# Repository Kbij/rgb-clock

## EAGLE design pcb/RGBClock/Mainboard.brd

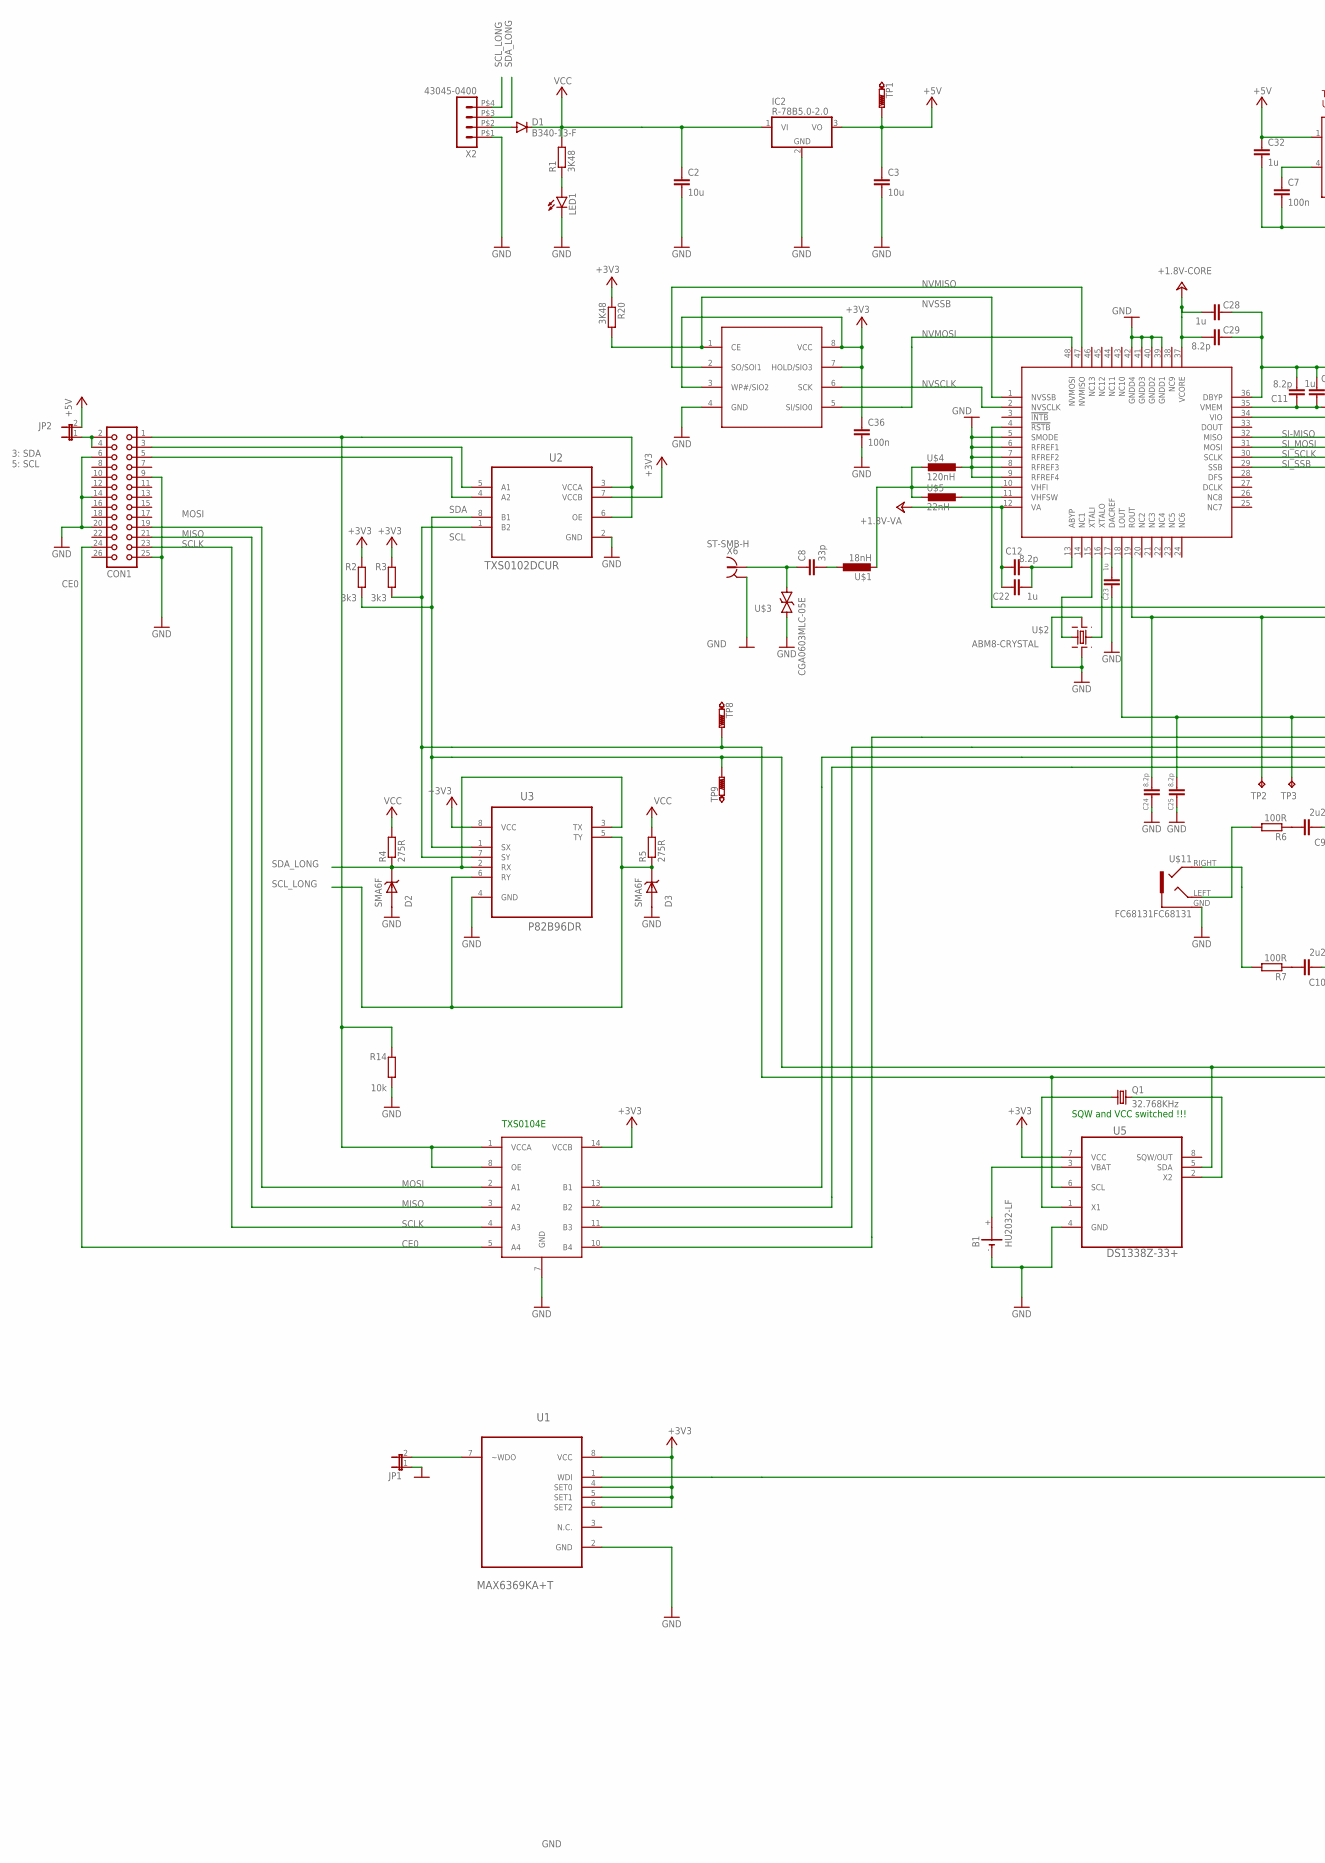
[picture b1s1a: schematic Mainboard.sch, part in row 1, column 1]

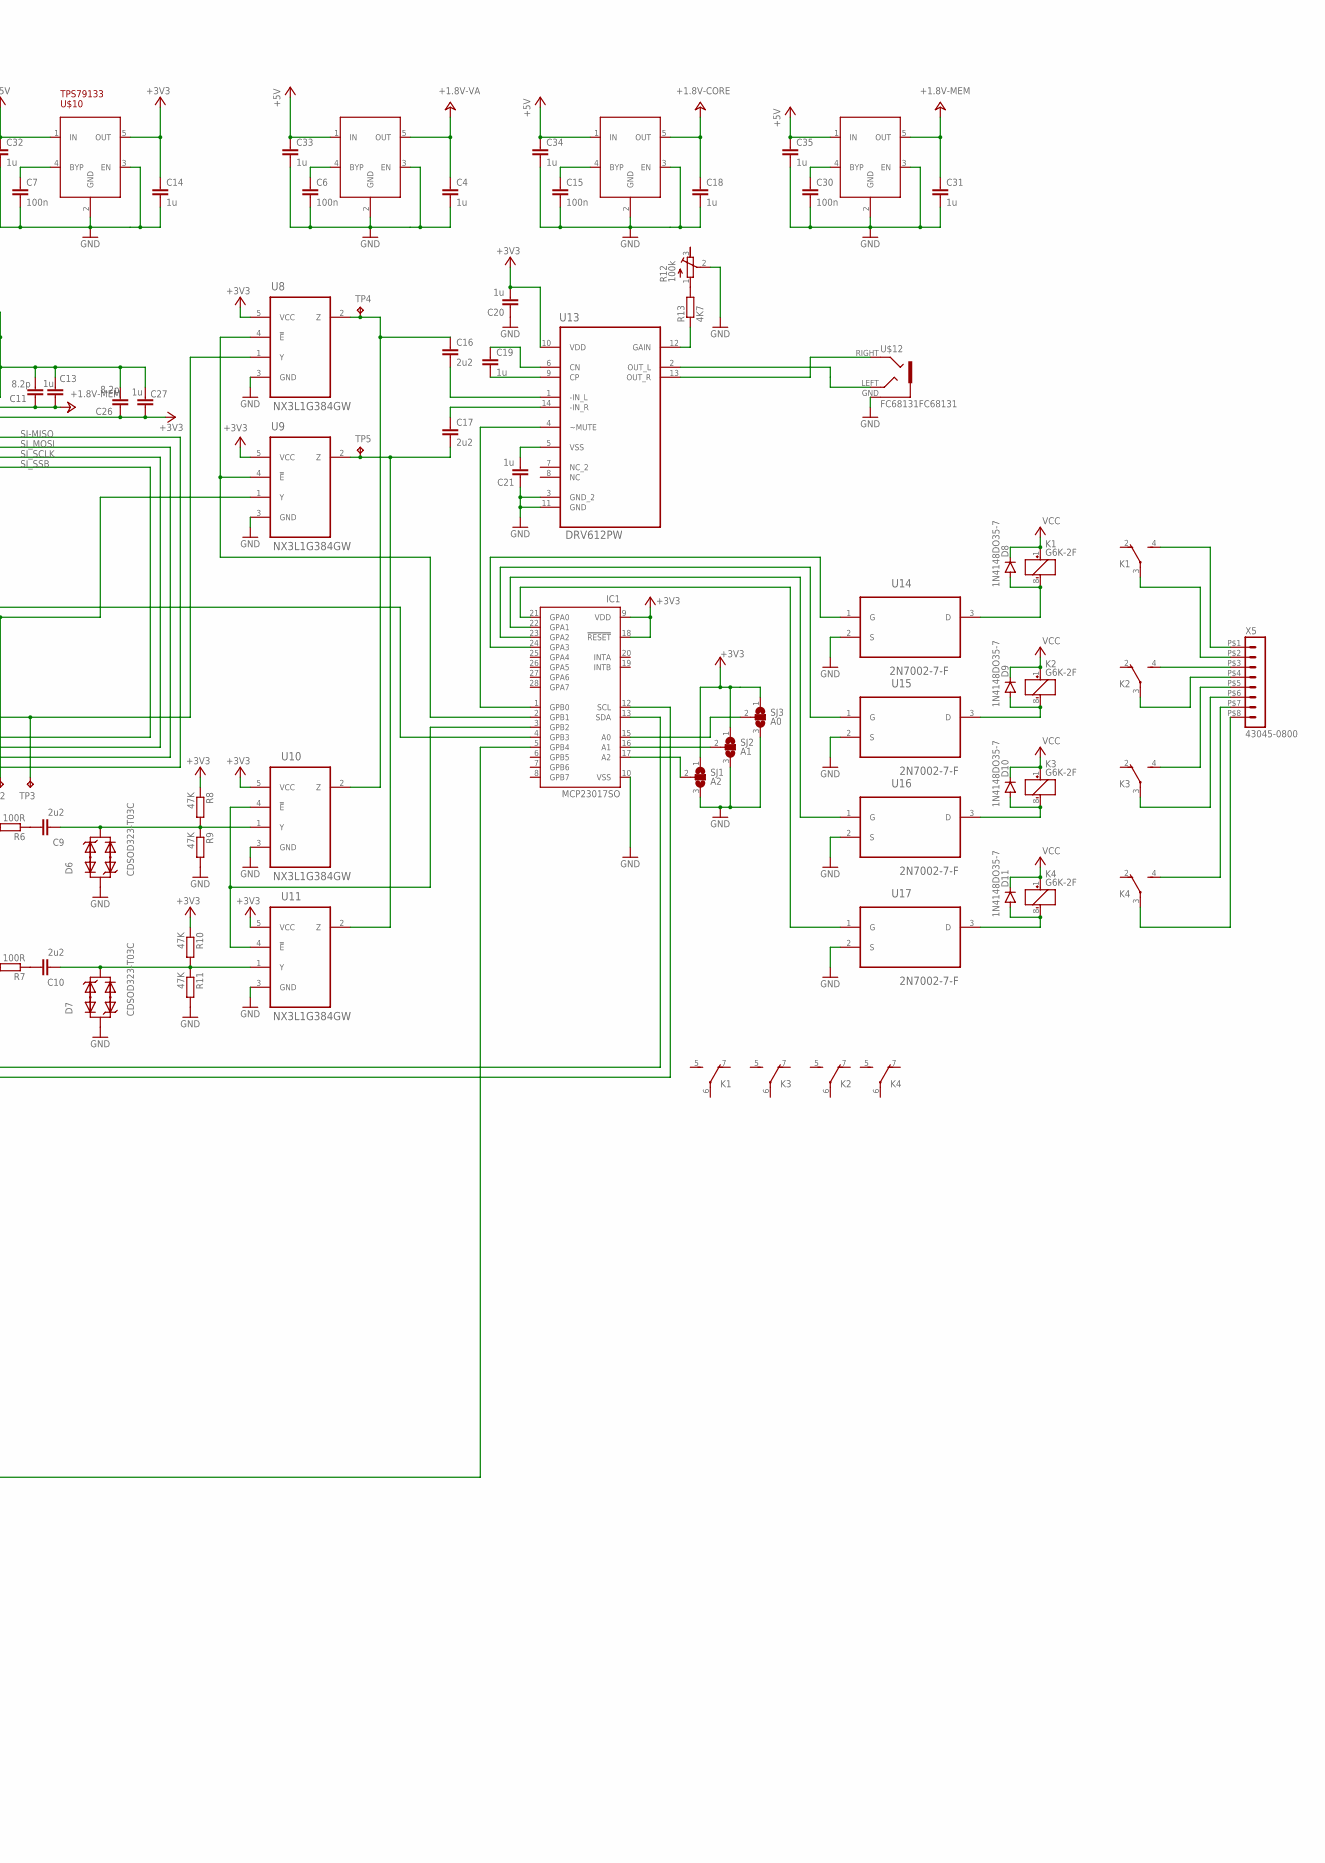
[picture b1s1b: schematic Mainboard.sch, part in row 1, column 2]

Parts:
B1: HU2032-LF; MYCOMPONENTS_HU2032-LF
C2, C3: 10u; RCL_C1206
C4, C13, C14, C18, C22, C23, C27, C28, C31, C32, C33, C34, C35: 1u; RCL_C0805
C6, C7, C15, C30, C36: 100n; RCL_C0805
C8: 33p; RCL_C0805
C9, C10, C16, C17: 2u2; RCL_C0805
C11, C12, C24, C25, C26, C29: 8.2p; RCL_C0805
C19, C20, C21: 1u; RCL_C1005
CON1: CON26
D1: B340-13-F; DIODE_DO-214AC
D2, D3: SMA6F; MYCOMPONENTS_DO-221AC
D6, D7: CDSOD323-T03C; MYCOMPONENTS_SOD323
D8, D9, D10, D11: 1N4148DO35-7; DIODE_DO35-7
IC1: MCP23017SO; MICROCHIP_SO28W
IC2: R-78B5.0-2.0; TO220V
JP1, JP2: JUMPER_JP1E; JUMPER_JP1
K1, K2, K3, K4: G6K-2F; RELAY_G6K-2F
LED1: LEDCHIP-LED0805; CHIP-LED0805
Q1: 32.768KHz; CRYSTAL_TC26V
R1, R20: 3K48; M0805
R2, R3: 3k3; M0805
R4, R5: 275R; M0805
R6, R7: 100R; M0805
R8, R9, R10, R11: 47K; M0805
R12: 100k; RESISTOR_RTRIM4G/J
R13: 4K7; M0805
R14: 10k; M0805
SJ1: A2; SJ_2
SJ2: A1; SJ_2
SJ3: A0; SJ_2
SPI: TXS0104E; TEXAS_SOP65P640X120-14N
TP1, TP8, TP9: PTR1PAD1-13; P1-13
TP2, TP3, TP4, TP5: TESTPAD_TPTP07SQ; TESTPAD_TP07SQ
U1: MAX6369KA+T; MAXIM_BY_ELEMENT14_BATCH_1_SOT65P280X145-8N
U2: TXS0102DCUR; TEXAS_SOP50P310X90-8N
U3: P82B96DR; TEXAS_SOIC127P600X175-8N
U5: DS1338Z-33+; MAXIM_BY_ELEMENT14_BATCH_1_SOIC127P600X175-8N
U8, U9, U10, U11: NX3L1G384GW; NXP_BY_ELEMENT14_BATCH_1_SOT65P212X110-5N
U13: DRV612PW; TEXAS_SOP65P640X120-14N
U14, U15, U16, U17: 2N7002-7-F; DIODES_SOT103P240X110-3N
U$1: 18nH; MAINBOARD_0603
U$2: ABM8-CRYSTAL; ABM8
U$3: CGA0603MLC-05E; MAINBOARD_C0603K
U$4: 120nH; MAINBOARD_0603
U$5: 22nH; MAINBOARD_0603
U$6: SI4684-MYSMD; QFN48-SI4684
U$7, U$8, U$9: TPS79118; SOT23-5
U$10: TPS79133; SOT23-5
U$11, U$12: FC68131FC68131; FC68131
U$13: SST26VF032B; SOIJ8
X2: 43045-0400; CON-MOLEX-MICRO-FIT-3_0_43045-0400
X5: 43045-0800; CON-MOLEX-MICRO-FIT-3_0_43045-0800
X6: ST-SMB-H; MAINBOARD_ST-SMB-H

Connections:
+1.8-MEM: C11.1, C13.1, C31.1, U$6.35 (VMEM), U$9.5 (OUT)
+1.8-VA: C4.1, C12.1, C22.1, U$6.12 (VA), U$7.5 (OUT)
+1.8-VCORE: C18.1, C28.2, C29.2, U$6.37 (VCORE), U$8.5 (OUT)
+3V3: C14.1, C20.2, C26.1, C27.1, C36.1, IC1.9 (VDD), IC1.18 (!RESET), R2.2, R3.2, R8.1, R10.1, R20.1, SJ1.1, SJ2.1, SJ3.1, SPI.14 (VCCB), U1.4 (SET0), U1.5 (SET1), U1.6 (SET2), U1.8 (VCC), U2.7 (VCCB), U3.8 (VCC), U5.7 (VCC), U8.5 (VCC), U9.5 (VCC), U10.5 (VCC), U11.5 (VCC), U13.10 (VDD), U$6.34 (VIO), U$10.5 (OUT), U$13.3 (WP#/SIO2), U$13.7 (HOLD/SIO3), U$13.8 (VCC)
+5V: C3.1, C32.1, C33.1, C34.1, C35.1, IC2.3 (VO), JP2.2, TP1.TP, U$7.1 (IN), U$8.1 (IN), U$9.1 (IN), U$10.1 (IN)
CE0: CON1.24, SPI.5 (A4)
GND: B1.-, C2.2, C3.2, C4.2, C6.2, C7.2, C14.2, C15.2, C18.2, C20.1, C21.1, C23.1, C24.1, C25.1, C30.2, C31.2, C32.2, C33.2, C34.2, C35.2, C36.2, CON1.6, CON1.9, CON1.14, CON1.20, CON1.25, D2.AN, D3.AN, D6.P$1, D7.P$1, IC1.10 (VSS), IC2.2 (GND), JP1.1, LED1.C, R9.2, R11.2, R12.2 (S), R14.1, SJ1.3, SJ2.3, SJ3.3, SPI.7 (GND), U1.2 (GND), U2.2 (GND), U3.4 (GND), U5.4 (GND), U8.3 (GND), U9.3 (GND), U10.3 (GND), U11.3 (GND), U13.3 (GND_2), U13.11 (GND), U14.2 (S), U15.2 (S), U16.2 (S), U17.2 (S), U$2.1 (GND1), U$2.3 (GND2), U$3.1, U$4.1, U$6.5 (SMODE), U$6.6 (RFREF1), U$6.7 (RFREF2), U$6.8 (RFREF3), U$6.9 (RFREF4), U$6.39 (GNDD1), U$6.40 (GNDD2), U$6.41 (GNDD3), U$6.42 (GNDD4), U$7.2 (GND), U$7.3 (EN), U$8.2 (GND), U$8.3 (EN), U$9.2 (GND), U$9.3 (EN), U$10.2 (GND), U$10.3 (EN), U$11.GND, U$12.GND, U$13.4 (GND), X2.P$1 (1), X6.2, X6.3 (2), X6.4 (2), X6.5 (2)
MISO: CON1.21, SPI.3 (A2)
MOSI: CON1.19, SPI.2 (A1)
unnamed: D1.A, X2.P$2 (2)
unnamed: U$2.2 (1), U$6.15 (XTALI)
unnamed: CON1.3, U2.5 (A1)
unnamed: CON1.2, CON1.4, JP2.1
unnamed: K1.4 (S), X5.P$1 (1)
unnamed: CON1.5, U2.4 (A2)
unnamed: IC1.21 (GPA0), U17.1 (G)
unnamed: CON1.1, R14.2, SPI.1 (VCCA), SPI.8 (OE), U2.3 (VCCA), U2.6 (OE)
unnamed: D11.A, K4.8 (-), U17.3 (D)
unnamed: IC1.17 (A2), SJ1.2
unnamed: IC1.16 (A1), SJ2.2
unnamed: K4.4 (S), X5.P$7 (7)
unnamed: K4.3, X5.P$8 (8)
unnamed: LED1.A, R1.1
unnamed: Q1.2, U5.2 (X2)
unnamed: B1.+, U5.3 (VBAT)
unnamed: Q1.1, U5.1 (X1)
unnamed: IC1.24 (GPA3), U14.1 (G)
unnamed: IC1.23 (GPA2), U15.1 (G)
unnamed: K1.3, X5.P$2 (2)
unnamed: IC1.22 (GPA1), U16.1 (G)
unnamed: D8.A, K1.8 (-), U14.3 (D)
unnamed: D9.A, K2.8 (-), U15.3 (D)
unnamed: D10.A, K3.8 (-), U16.3 (D)
unnamed: U$2.4 (2), U$6.16 (XTALO)
unnamed: C25.2, TP3.TP, U8.1 (Y), U$6.18 (LOUT)
unnamed: C8.1, U$3.2, X6.1
unnamed: C16.1, TP4.TP, U8.2 (Z), U10.2 (Z)
unnamed: C17.2, TP5.TP, U9.2 (Z), U11.2 (Z)
unnamed: IC1.3 (GPB2), U10.4 (!E), U11.4 (!E)
unnamed: U$5.1, U$6.11 (VHFSW)
unnamed: IC1.5 (GPB4), U1.1 (WDI)
unnamed: C24.2, TP2.TP, U9.1 (Y), U$6.19 (ROUT)
unnamed: IC1.4 (GPB3), U$6.4 (!RSTB)
unnamed: C10.2, D7.P$2, R10.2, R11.1, U11.1 (Y)
unnamed: C9.2, D6.P$2, R8.2, R9.1, U10.1 (Y)
unnamed: IC1.1 (GPB0), U13.4 (~MUTE)
unnamed: C6.1, U$7.4 (BYP)
unnamed: U13.2 (OUT_L), U$12.LEFT
unnamed: IC1.15 (A0), SJ3.2
unnamed: U13.13 (OUT_R), U$12.RIGHT
unnamed: R12.1 (E), R13.2
unnamed: R13.1, U13.12 (GAIN)
unnamed: R6.2, U$11.LEFT
unnamed: C9.1, R6.1
unnamed: R7.2, U$11.RIGHT
unnamed: C10.1, R7.1
unnamed: JP1.2, U1.7 (~WDO)
unnamed: K2.4 (S), X5.P$3 (3)
unnamed: C16.2, U13.1 (-IN_L)
unnamed: C19.2, U13.9 (CP)
unnamed: C17.1, U13.14 (-IN_R)
unnamed: C19.1, U13.6 (CN)
unnamed: C21.2, U13.5 (VSS)
unnamed: C15.1, U$8.4 (BYP)
unnamed: U$1.2, U$4.2, U$5.2, U$6.10 (VHFI)
unnamed: K2.3, X5.P$4 (4)
unnamed: C8.2, U$1.1
unnamed: C30.1, U$9.4 (BYP)
unnamed: K3.4 (S), X5.P$5 (5)
unnamed: K3.3, X5.P$6 (6)
unnamed: C7.1, U$10.4 (BYP)
unnamed: IC1.2 (GPB1), U8.4 (!E), U9.4 (!E)
unnamed: C12.2, C22.2, U$6.13 (ABYP)
unnamed: C23.2, U$6.17 (DACREF)
unnamed: C11.2, C13.2, C26.2, C27.2, C28.1, C29.1, U$6.36 (DBYP)
NVMISO: U$6.47 (NVMISO), U$13.2 (SO/SOI1)
NVMOSI: U$6.48 (NVMOSI), U$13.5 (SI/SIO0)
NVSCLK: U$6.2 (NVSCLK), U$13.6 (SCK)
NVSSB: R20.2, U$6.1 (NVSSB), U$13.1 (CE)
SCL: IC1.12 (SCL), R3.1, TP8.TP, U2.1 (B2), U3.7 (SY), U5.6 (SCL)
SCLK: CON1.23, SPI.4 (A3)
SCL_LONG: D3.KAT, R5.1, U3.5 (TY), U3.6 (RY), X2.P$4 (4)
SDA: IC1.13 (SDA), R2.1, TP9.TP, U2.8 (B1), U3.1 (SX), U5.5 (SDA)
SDA_LONG: D2.KAT, R4.1, U3.2 (RX), U3.3 (TX), X2.P$3 (3)
SI-MISO: SPI.12 (B2), U$6.32 (MISO)
SI_MOSI: SPI.13 (B1), U$6.31 (MOSI)
SI_SCLK: SPI.11 (B3), U$6.30 (SCLK)
SI_SSB: SPI.10 (B4), U$6.29 (SSB)
VCC: C2.1, D1.C, D8.C, D9.C, D10.C, D11.C, IC2.1 (VI), K1.1 (+), K2.1 (+), K3.1 (+), K4.1 (+), R1.2, R4.2, R5.2

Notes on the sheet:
3: SDA 5: SCL
SDA
SCL
TXS0104E
SQW and VCC switched !!!

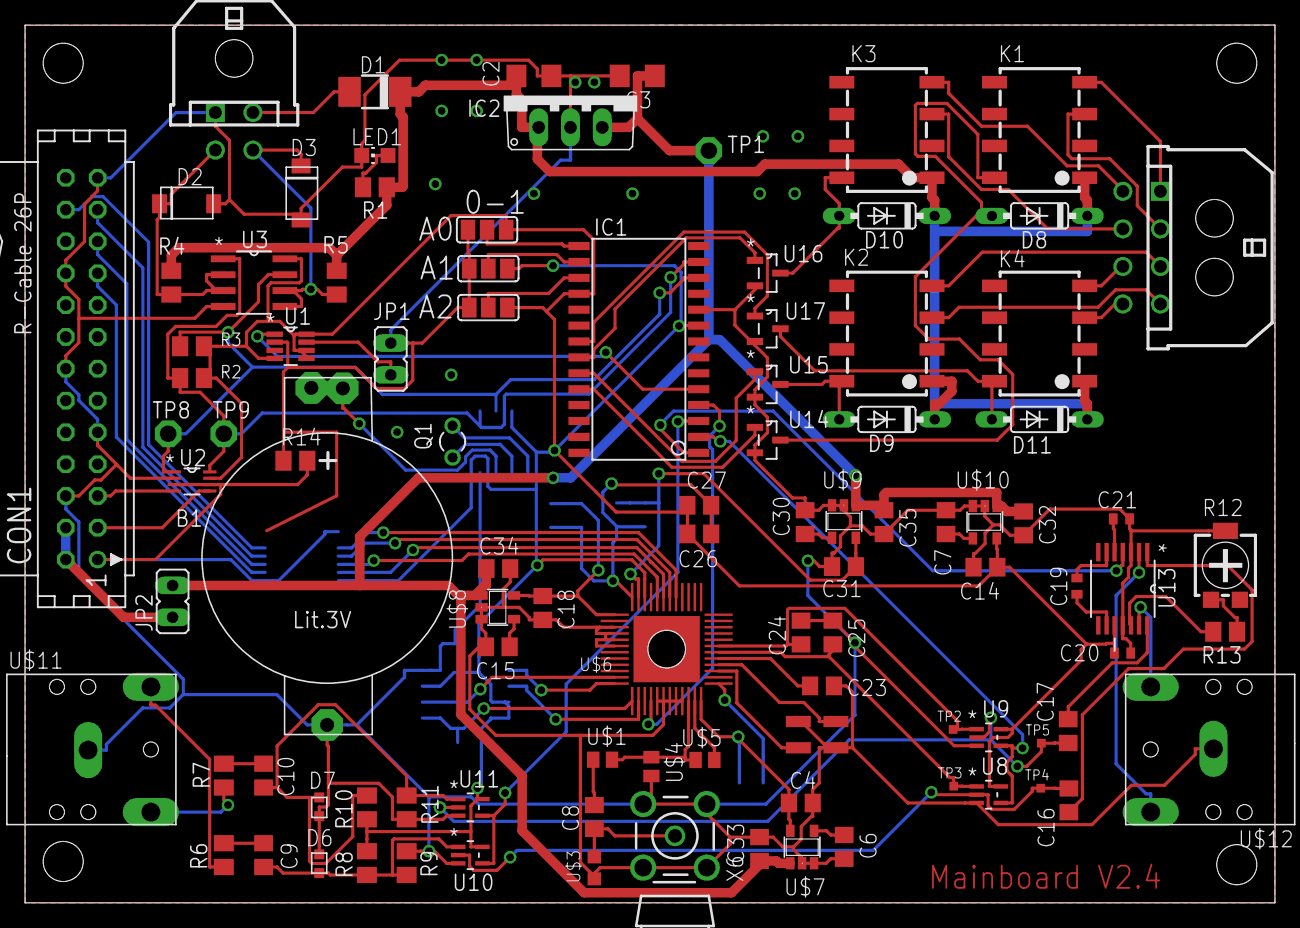
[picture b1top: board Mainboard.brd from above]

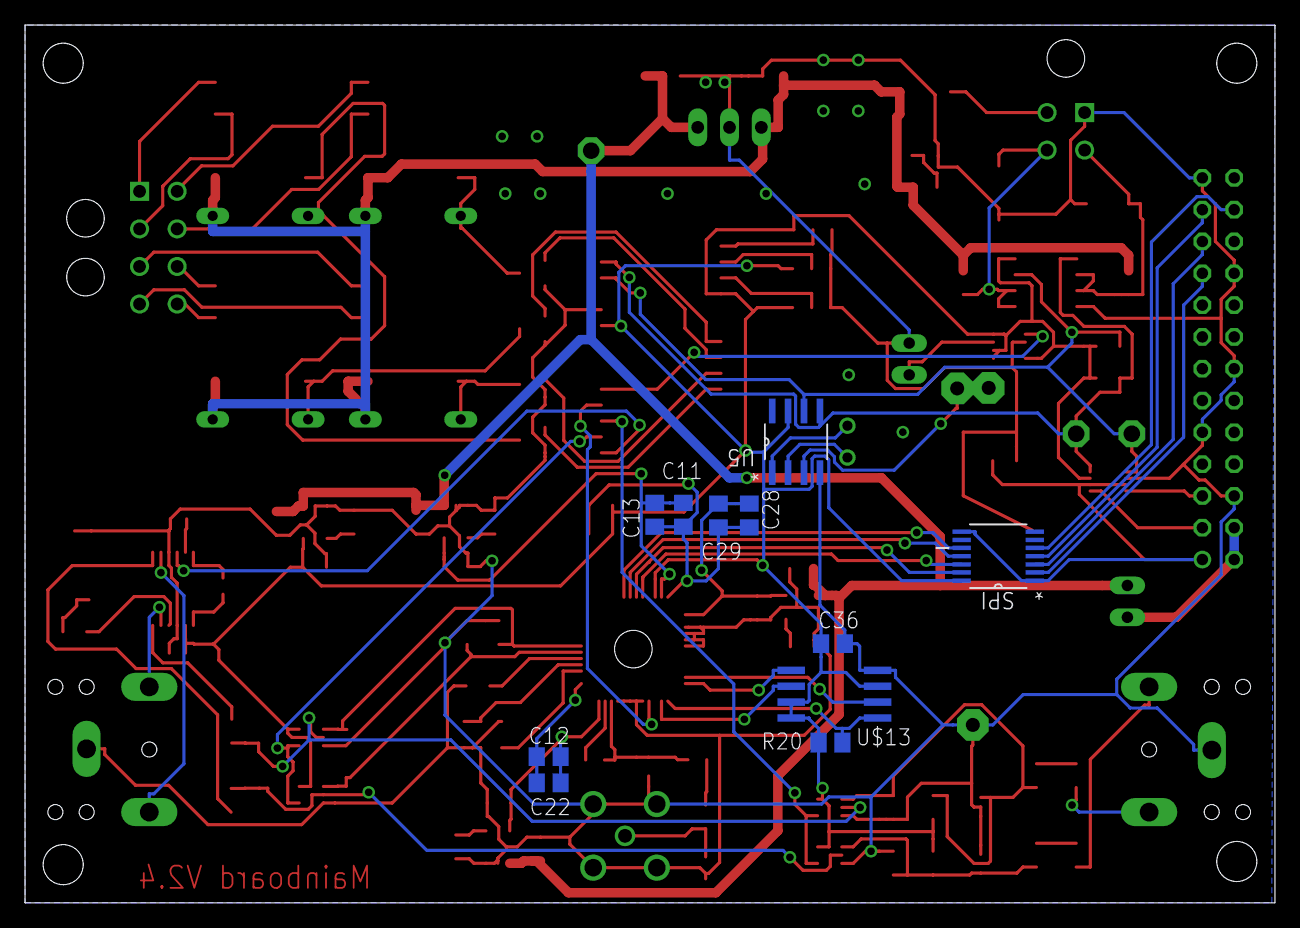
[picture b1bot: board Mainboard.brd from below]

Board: 2 copper layers, 99.8 x 70.1 mm, 110 parts (11 on the bottom side), 89 nets.

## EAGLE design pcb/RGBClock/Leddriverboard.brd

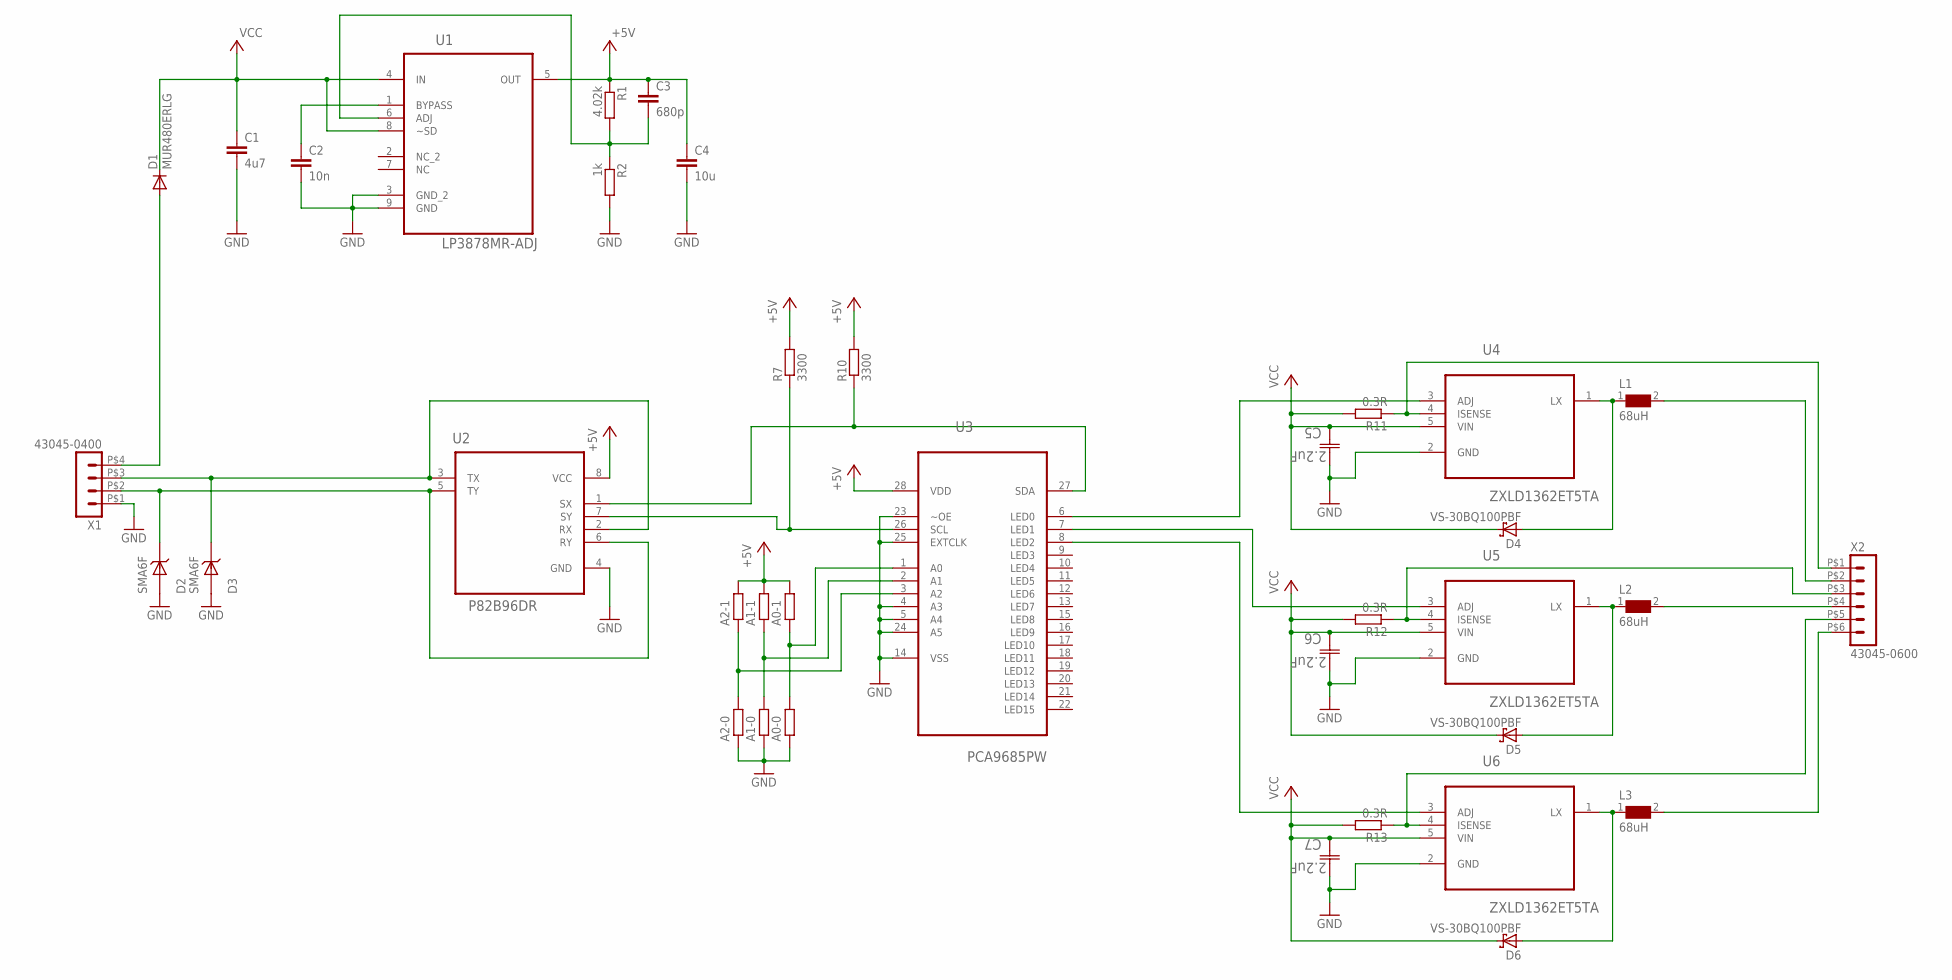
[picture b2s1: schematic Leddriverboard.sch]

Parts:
C1: 4u7; C0805
C2: 10n; C0805
C3: 680p; C0805
C4: 10u; C0805
C5, C6, C7: 2.2uF; CAPC2013X152N
D1: MUR480ERLG; DO41-10
D2, D3: SMA6F; DO-221AC
D4, D5, D6: VS-30BQ100PBF; DO-214AB
L1, L2, L3: 68uH; L
R1: 4.02k; R0603
R2: 1k; R0603
R3: A2-1; R0402
R4: A2-0; R0402
R5: A1-1; R0402
R6: A1-0; R0402
R7, R10: 3300; 0204/7
R8: A0-1; R0402
R9: A0-0; R0402
R11, R12, R13: 0.3R; R0603
U1: LP3878MR-ADJ; SOIC127P600X168-8N
U2: P82B96DR; SOIC127P600X175-8N
U3: PCA9685PW; SOP65P640X110-28N
U4, U5, U6: ZXLD1362ET5TA; SOT95P270X145-5N
X1: 43045-0400
X2: 43045-0600

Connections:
+5V: C3.1, C4.1, R1.1, R3.2, R5.2, R7.2, R8.2, R10.2, U1.5 (OUT), U2.8 (VCC), U3.28 (VDD)
GND: C1.2, C2.2, C4.2, C5.1 (C1), C6.1 (C1), C7.1 (C1), D2.AN, D3.AN, R2.2, R4.1, R6.1, R9.1, U1.3 (GND_2), U1.9 (GND), U2.4 (GND), U3.4 (A3), U3.5 (A4), U3.14 (VSS), U3.23 (~OE), U3.24 (A5), U3.25 (EXTCLK), U4.2 (GND), U5.2 (GND), U6.2 (GND), X1.P$1 (1)
unnamed: R11.1, U4.4 (ISENSE), X2.P$1 (1)
unnamed: U3.7 (LED1), U5.3 (ADJ)
unnamed: R12.1, U5.4 (ISENSE), X2.P$3 (3)
unnamed: L2.2, X2.P$4 (4)
unnamed: L1.2, X2.P$2 (2)
unnamed: D3.KAT, U2.2 (RX), U2.3 (TX), X1.P$3 (3)
unnamed: U3.6 (LED0), U4.3 (ADJ)
unnamed: D5.A, L2.1, U5.1 (LX)
unnamed: D4.A, L1.1, U4.1 (LX)
unnamed: U3.8 (LED2), U6.3 (ADJ)
unnamed: R13.1, U6.4 (ISENSE), X2.P$5 (5)
unnamed: L3.2, X2.P$6 (6)
unnamed: D6.A, L3.1, U6.1 (LX)
unnamed: D2.KAT, U2.5 (TY), U2.6 (RY), X1.P$2 (2)
unnamed: C3.2, R1.2, R2.1, U1.6 (ADJ)
unnamed: D1.A, X1.P$4 (4)
unnamed: C2.1, U1.1 (BYPASS)
unnamed: R8.1, R9.2, U3.1 (A0)
unnamed: R5.1, R6.2, U3.2 (A1)
unnamed: R3.1, R4.2, U3.3 (A2)
SCL: R7.1, U2.7 (SY), U3.26 (SCL)
SDA: R10.1, U2.1 (SX), U3.27 (SDA)
VCC: C1.1, C5.2 (C2), C6.2 (C2), C7.2 (C2), D1.C, D4.K (C), D5.K (C), D6.K (C), R11.2, R12.2, R13.2, U1.4 (IN), U1.8 (~SD), U4.5 (VIN), U5.5 (VIN), U6.5 (VIN)

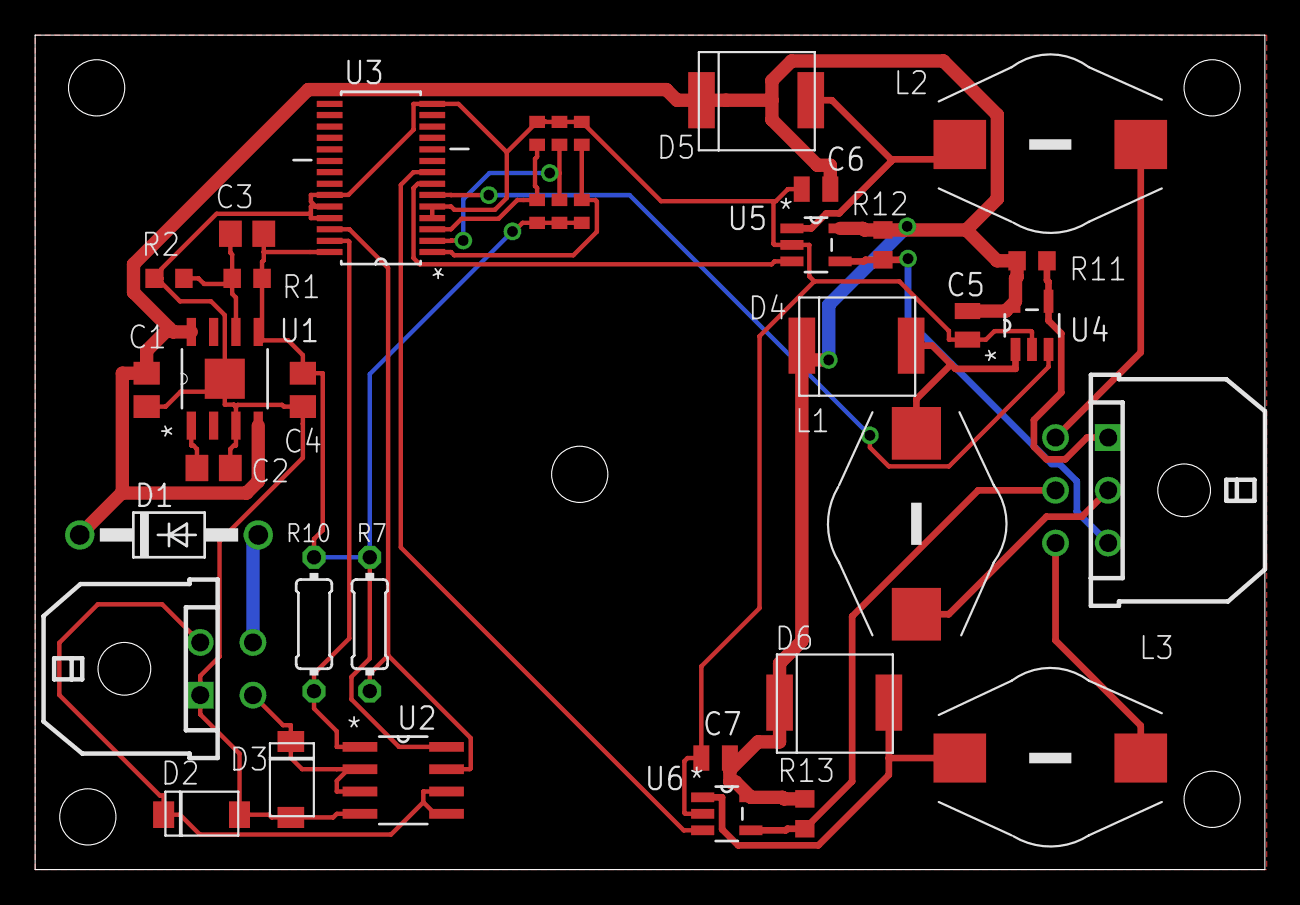
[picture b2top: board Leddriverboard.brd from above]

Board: 2 copper layers, 70.0 x 47.5 mm, 37 parts (0 on the bottom side), 25 nets.

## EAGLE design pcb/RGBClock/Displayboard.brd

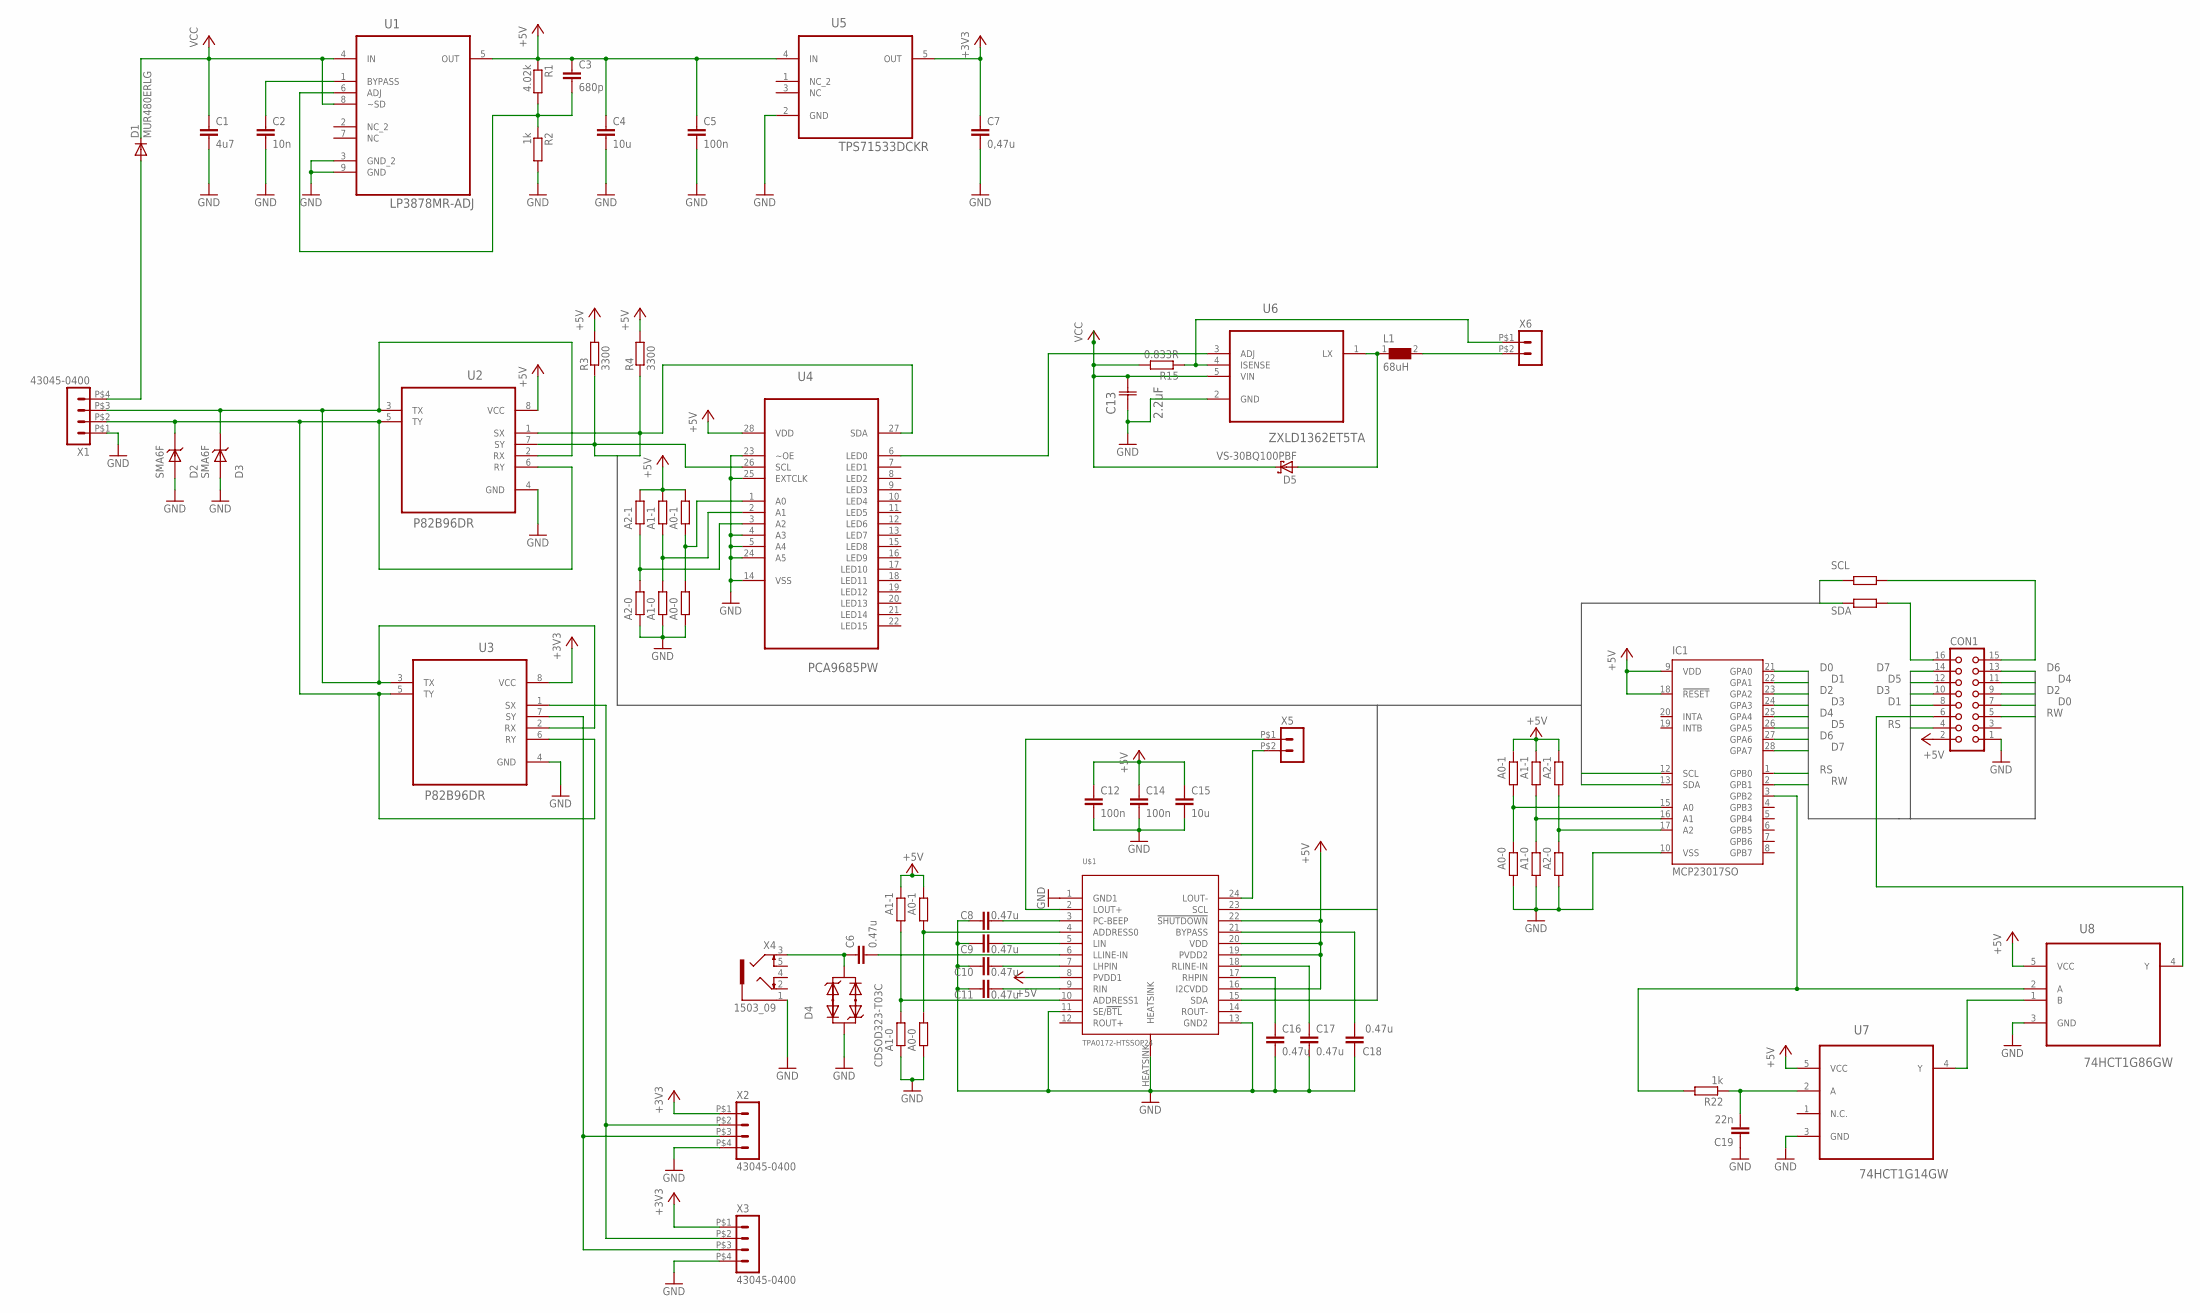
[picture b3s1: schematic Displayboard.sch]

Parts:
C1: 4u7; C1206
C2: 10n; C1608
C3: 680p; C1608
C4, C15: 10u; C2012
C5, C12, C14: 100n; C0805
C6, C8, C9, C10, C11, C16, C17, C18: 0.47u; C0805
C7: 0,47u; C1206
C13: 2.2uF; CAPC2013X152N
C19: 22n; C0805
CON1: CON16
D1: MUR480ERLG; DO41-10
D2, D3: SMA6F; DO-221AC
D4: CDSOD323-T03C; SOD323
D5: VS-30BQ100PBF; DO-214AB
IC1: MCP23017SO; SO28W
L1: 68uH; L
R1: 4.02k; R0603
R2: 1k; R0603
R3, R4: 3300; 0204/7
R5, R20: A2-1; R0402
R6, R21: A2-0; R0402
R7, R11, R18: A1-1; R0402
R8, R12, R19: A1-0; R0402
R9, R13, R16: A0-1; R0402
R10, R14, R17: A0-0; R0402
R15: 0.833R; R0603
R22: 1k; 0204/7
R23: SCL; R0402
R24: SDA; R0402
U1: LP3878MR-ADJ; SOIC127P600X168-8N
U2, U3: P82B96DR; SOIC127P600X175-8N
U4: PCA9685PW; SOP65P640X110-28N
U5: TPS71533DCKR; SOT65P210X110-5N
U6: ZXLD1362ET5TA; SOT95P270X145-5N
U7: 74HCT1G14GW; SOT65P210X110-5N
U8: 74HCT1G86GW; SOT65P210X110-5N
U$1: TPA0172-HTSSOP24; HT-TSSOP-24
X1, X2, X3: 43045-0400
X4: 1503_09
X5, X6: HEADER_POS2_43045-0200; 43045-0200

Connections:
+3V3: C7.1, U3.8 (VCC), U5.5 (OUT), X2.P$1 (1), X3.P$1 (1); also elsewhere on the board
+5V: C3.1, C4.1, C5.1, C12.1, C14.1, C15.1, CON1.2, IC1.9 (VDD), IC1.18 (!RESET), R1.1, R3.2, R4.2, R5.2, R7.2, R9.2, R11.2, R13.2, R16.2, R18.2, R20.2, U1.5 (OUT), U2.8 (VCC), U4.28 (VDD), U5.4 (IN), U7.5 (VCC), U8.5 (VCC), U$1.8 (PVDD1), U$1.16 (I2CVDD), U$1.19 (PVDD2), U$1.20 (VDD), U$1.22 (!SHUTDOWN); also elsewhere on the board
D0: CON1.7, IC1.21 (GPA0); also elsewhere on the board
D1: CON1.8, IC1.22 (GPA1); also elsewhere on the board
D2: CON1.9, IC1.23 (GPA2); also elsewhere on the board
D3: CON1.10, IC1.24 (GPA3); also elsewhere on the board
D4: CON1.11, IC1.25 (GPA4); also elsewhere on the board
D5: CON1.12, IC1.26 (GPA5); also elsewhere on the board
D6: CON1.13, IC1.27 (GPA6); also elsewhere on the board
D7: CON1.14, IC1.28 (GPA7); also elsewhere on the board
GND: C1.2, C2.2, C4.2, C5.2, C7.2, C8.1, C9.1, C10.1, C11.1, C12.2, C13.1 (C1), C14.2, C15.2, C16.2, C17.2, C18.1, C19.1, CON1.1, D2.AN, D3.AN, D4.P$1, IC1.10 (VSS), R2.2, R6.1, R8.1, R10.1, R12.1, R14.1, R17.1, R19.1, R21.1, U1.3 (GND_2), U1.9 (GND), U2.4 (GND), U3.4 (GND), U4.4 (A3), U4.5 (A4), U4.14 (VSS), U4.23 (~OE), U4.24 (A5), U4.25 (EXTCLK), U5.2 (GND), U6.2 (GND), U7.3 (GND), U8.3 (GND), U$1.1 (GND1), U$1.11 (SE/!BTL), U$1.13 (GND2), U$1.HEATSINK, X1.P$1 (1), X2.P$4 (4), X3.P$4 (4), X4.1; also elsewhere on the board
unnamed: R15.1, U6.4 (ISENSE), X6.P$1 (1)
unnamed: D3.KAT, U2.2 (RX), U2.3 (TX), U3.2 (RX), U3.3 (TX), X1.P$3 (3)
unnamed 13: IC1.3 (GPB2), R22.2, U8.2 (A); also elsewhere on the board
unnamed 14: C16.1, U$1.17 (RHPIN); also elsewhere on the board
unnamed 15: C17.1, U$1.18 (RLINE-IN); also elsewhere on the board
unnamed: L1.2, X6.P$2 (2)
unnamed 17: U3.1 (SX), X2.P$2 (2), X3.P$2 (2); also elsewhere on the board
unnamed: U4.6 (LED0), U6.3 (ADJ)
unnamed 19: U3.7 (SY), X2.P$3 (3), X3.P$3 (3); also elsewhere on the board
unnamed: D5.A, L1.1, U6.1 (LX)
unnamed 21: U$1.24 (LOUT-), X5.P$2 (2); also elsewhere on the board
unnamed 22: U$1.2 (LOUT+), X5.P$1 (1); also elsewhere on the board
unnamed 23: C6.2, U$1.6 (LLINE-IN); also elsewhere on the board
unnamed 24: C11.2, U$1.9 (RIN); also elsewhere on the board
unnamed 25: C10.2, U$1.7 (LHPIN); also elsewhere on the board
unnamed 26: C9.2, U$1.5 (LIN); also elsewhere on the board
unnamed 27: C8.2, U$1.3 (PC-BEEP); also elsewhere on the board
unnamed 28: IC1.16 (A1), R18.1, R19.2; also elsewhere on the board
unnamed 29: IC1.15 (A0), R16.1, R17.2; also elsewhere on the board
unnamed: R5.1, R6.2, U4.3 (A2)
unnamed 31: IC1.17 (A2), R20.1, R21.2; also elsewhere on the board
unnamed: D2.KAT, U2.5 (TY), U2.6 (RY), U3.5 (TY), U3.6 (RY), X1.P$2 (2)
unnamed 33: C18.2, U$1.21 (BYPASS); also elsewhere on the board
unnamed: C3.2, R1.2, R2.1, U1.6 (ADJ)
unnamed: D1.A, X1.P$4 (4)
unnamed: C2.1, U1.1 (BYPASS)
unnamed: CON1.16, R24.1
unnamed: CON1.15, R23.1
unnamed: R7.1, R8.2, U4.2 (A1)
unnamed: C19.2, R22.1, U7.2 (A)
unnamed: U7.4 (Y), U8.1 (B)
unnamed: CON1.6, U8.4 (Y)
unnamed 44: R13.1, R14.2, U$1.4 (ADDRESS0); also elsewhere on the board
unnamed 45: R11.1, R12.2, U$1.10 (ADDRESS1); also elsewhere on the board
unnamed: R9.1, R10.2, U4.1 (A0)
unnamed: C6.1, D4.P$2, X4.3
RS: CON1.4, IC1.1 (GPB0); also elsewhere on the board
RW: CON1.5, IC1.2 (GPB1); also elsewhere on the board
SCL: IC1.12 (SCL), R3.1, R23.2, U2.7 (SY), U4.26 (SCL), U$1.23 (SCL); also elsewhere on the board
SDA: IC1.13 (SDA), R4.1, R24.2, U2.1 (SX), U4.27 (SDA), U$1.15 (SDA); also elsewhere on the board
VCC: C1.1, C13.2 (C2), D1.C, D5.K (C), R15.2, U1.4 (IN), U1.8 (~SD), U6.5 (VIN)
